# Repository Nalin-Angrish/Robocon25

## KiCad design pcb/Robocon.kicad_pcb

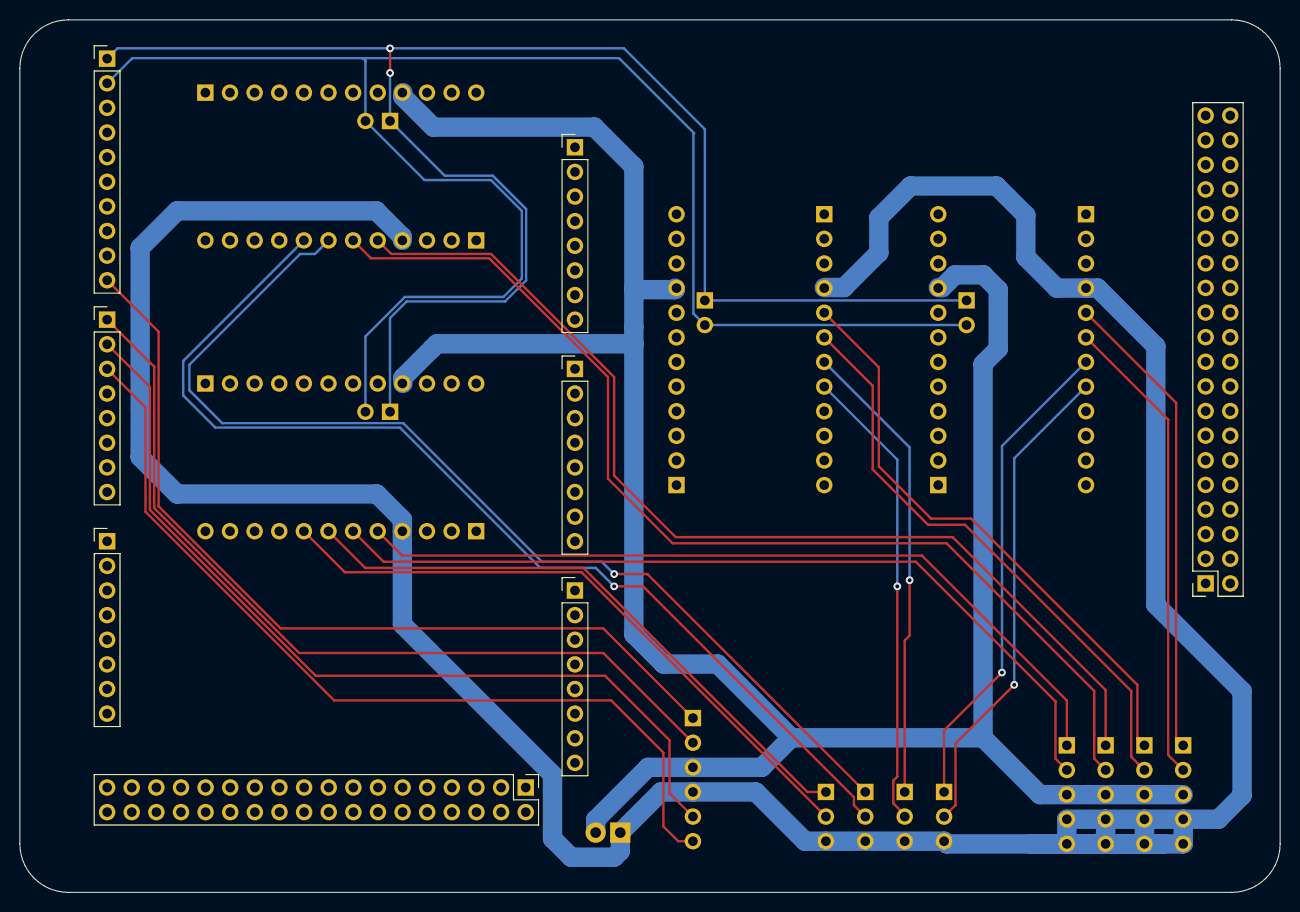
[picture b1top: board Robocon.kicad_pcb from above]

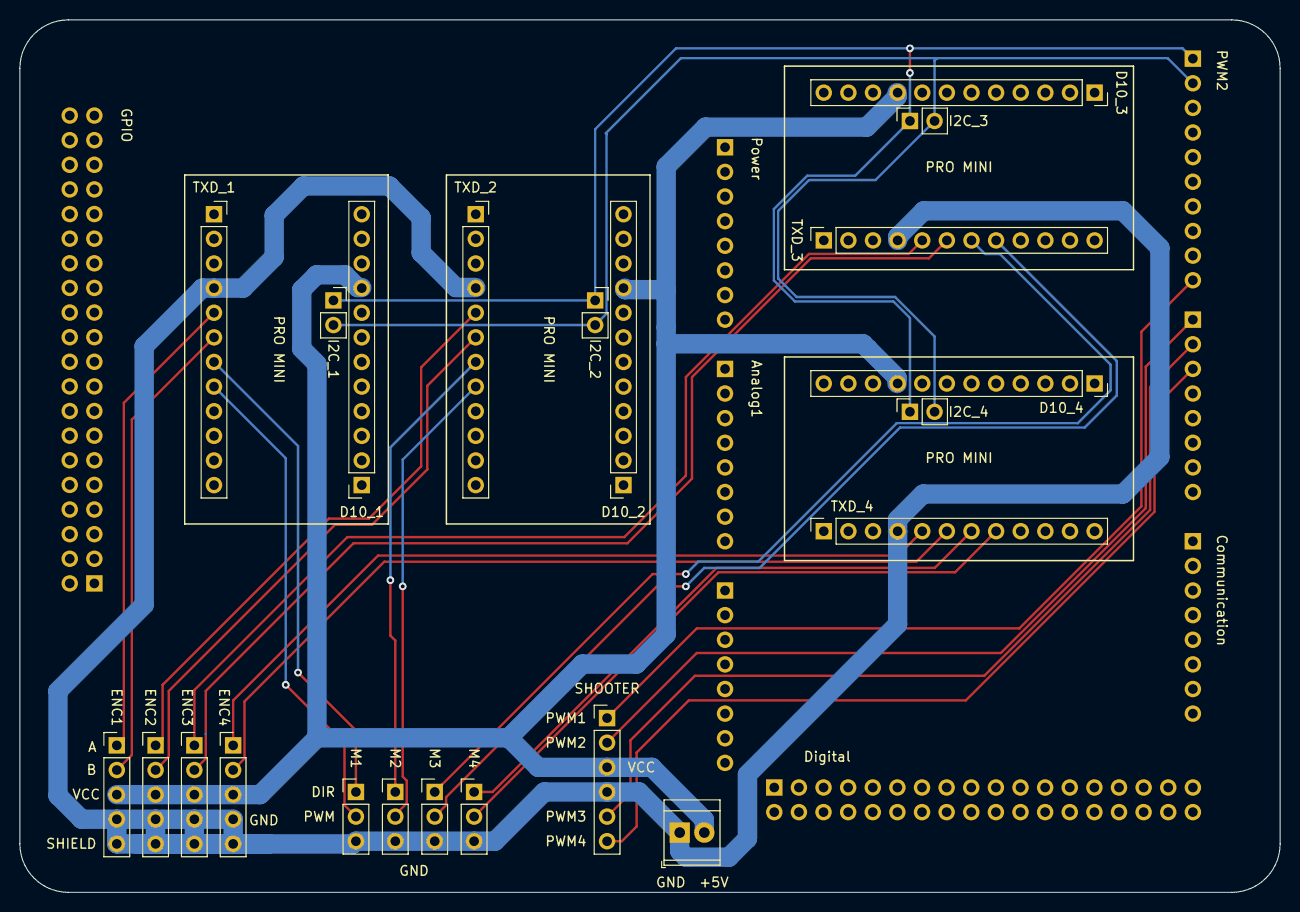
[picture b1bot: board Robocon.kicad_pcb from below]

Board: 2 copper layers, 130.0 x 90.0 mm, 30 parts (22 on the bottom side), 24 nets.

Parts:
Analog1: Analog1; PinHeader_1x08_P2.54mm_Vertical
Analog2: Analog2; PinHeader_1x08_P2.54mm_Vertical
Communication: Communication; PinHeader_1x08_P2.54mm_Vertical
D10_1, D10_2, D10_3, D10_4: Analog; PinSocket_1x12_P2.54mm_Vertical
Digital: Digital; PinHeader_2x18_P2.54mm_Vertical
ENC1, ENC2, ENC3, ENC4: PinHeader_1x05_P2.54mm_Vertical
GPIO: GPIO; PinSocket_2x20_P2.54mm_Vertical
I2C_1, I2C_2, I2C_3, I2C_4: PinSocket_1x02_P2.54mm_Vertical
M1, M2, M3, M4: PinHeader_1x03_P2.54mm_Vertical
PWM1: PWM1; PinHeader_1x08_P2.54mm_Vertical
PWM2: PWM2; PinHeader_1x10_P2.54mm_Vertical
PWR: TerminalBlock_TE_282834-2_1x02_P2.54mm_Horizontal
Power: Power; PinHeader_1x08_P2.54mm_Vertical
SHOOTER: PinHeader_1x06_P2.54mm_Vertical
TXD_1, TXD_2, TXD_3, TXD_4: Digital; PinSocket_1x12_P2.54mm_Vertical

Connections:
DIR_M1: M1.1, TXD_1.7
DIR_M2: M2.1, TXD_2.7
DIR_M3: M3.1, TXD_3.7
DIR_M4: M4.1, TXD_4.7
GND: ENC1.4, ENC1.5, ENC2.4, ENC2.5, ENC3.4, ENC3.5, ENC4.4, ENC4.5, M1.3, M2.3, M3.3, M4.3, PWR.1, SHOOTER.4, TXD_1.4, TXD_2.4, TXD_3.4, TXD_4.4
PA_M1: ENC1.1, TXD_1.5
PA_M2: ENC2.1, TXD_2.5
PA_M3: ENC3.1, TXD_3.5
PA_M4: ENC4.1, TXD_4.5
PB_M1: ENC1.2, TXD_1.6
PB_M2: ENC2.2, TXD_2.6
PB_M3: ENC3.2, TXD_3.6
PB_M4: ENC4.2, TXD_4.6
PWM1: PWM2.10, SHOOTER.1
PWM2: PWM1.1, SHOOTER.2
PWM3: PWM1.2, SHOOTER.5
PWM4: PWM1.3, SHOOTER.6
PWM_M1: M1.2, TXD_1.8
PWM_M2: M2.2, TXD_2.8
PWM_M3: M3.2, TXD_3.8
PWM_M4: M4.2, TXD_4.8
SCL: I2C_1.1, I2C_2.1, I2C_3.1, I2C_4.1, PWM2.1
SDA: I2C_1.2, I2C_2.2, I2C_3.2, I2C_4.2, PWM2.2
VCC: D10_1.9, D10_2.9, D10_3.9, D10_4.9, ENC1.3, ENC2.3, ENC3.3, ENC4.3, PWR.2, SHOOTER.3

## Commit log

2025-03-16 Stage-1
2025-03-16 Add STM32 Base
2025-03-16 Create Stepper motor - Test code
    Basic test code for checking the status of the stepper motor and the circuit board
2025-03-16 Add encoder code for single motor
2025-06-28 Upload PCB Files
